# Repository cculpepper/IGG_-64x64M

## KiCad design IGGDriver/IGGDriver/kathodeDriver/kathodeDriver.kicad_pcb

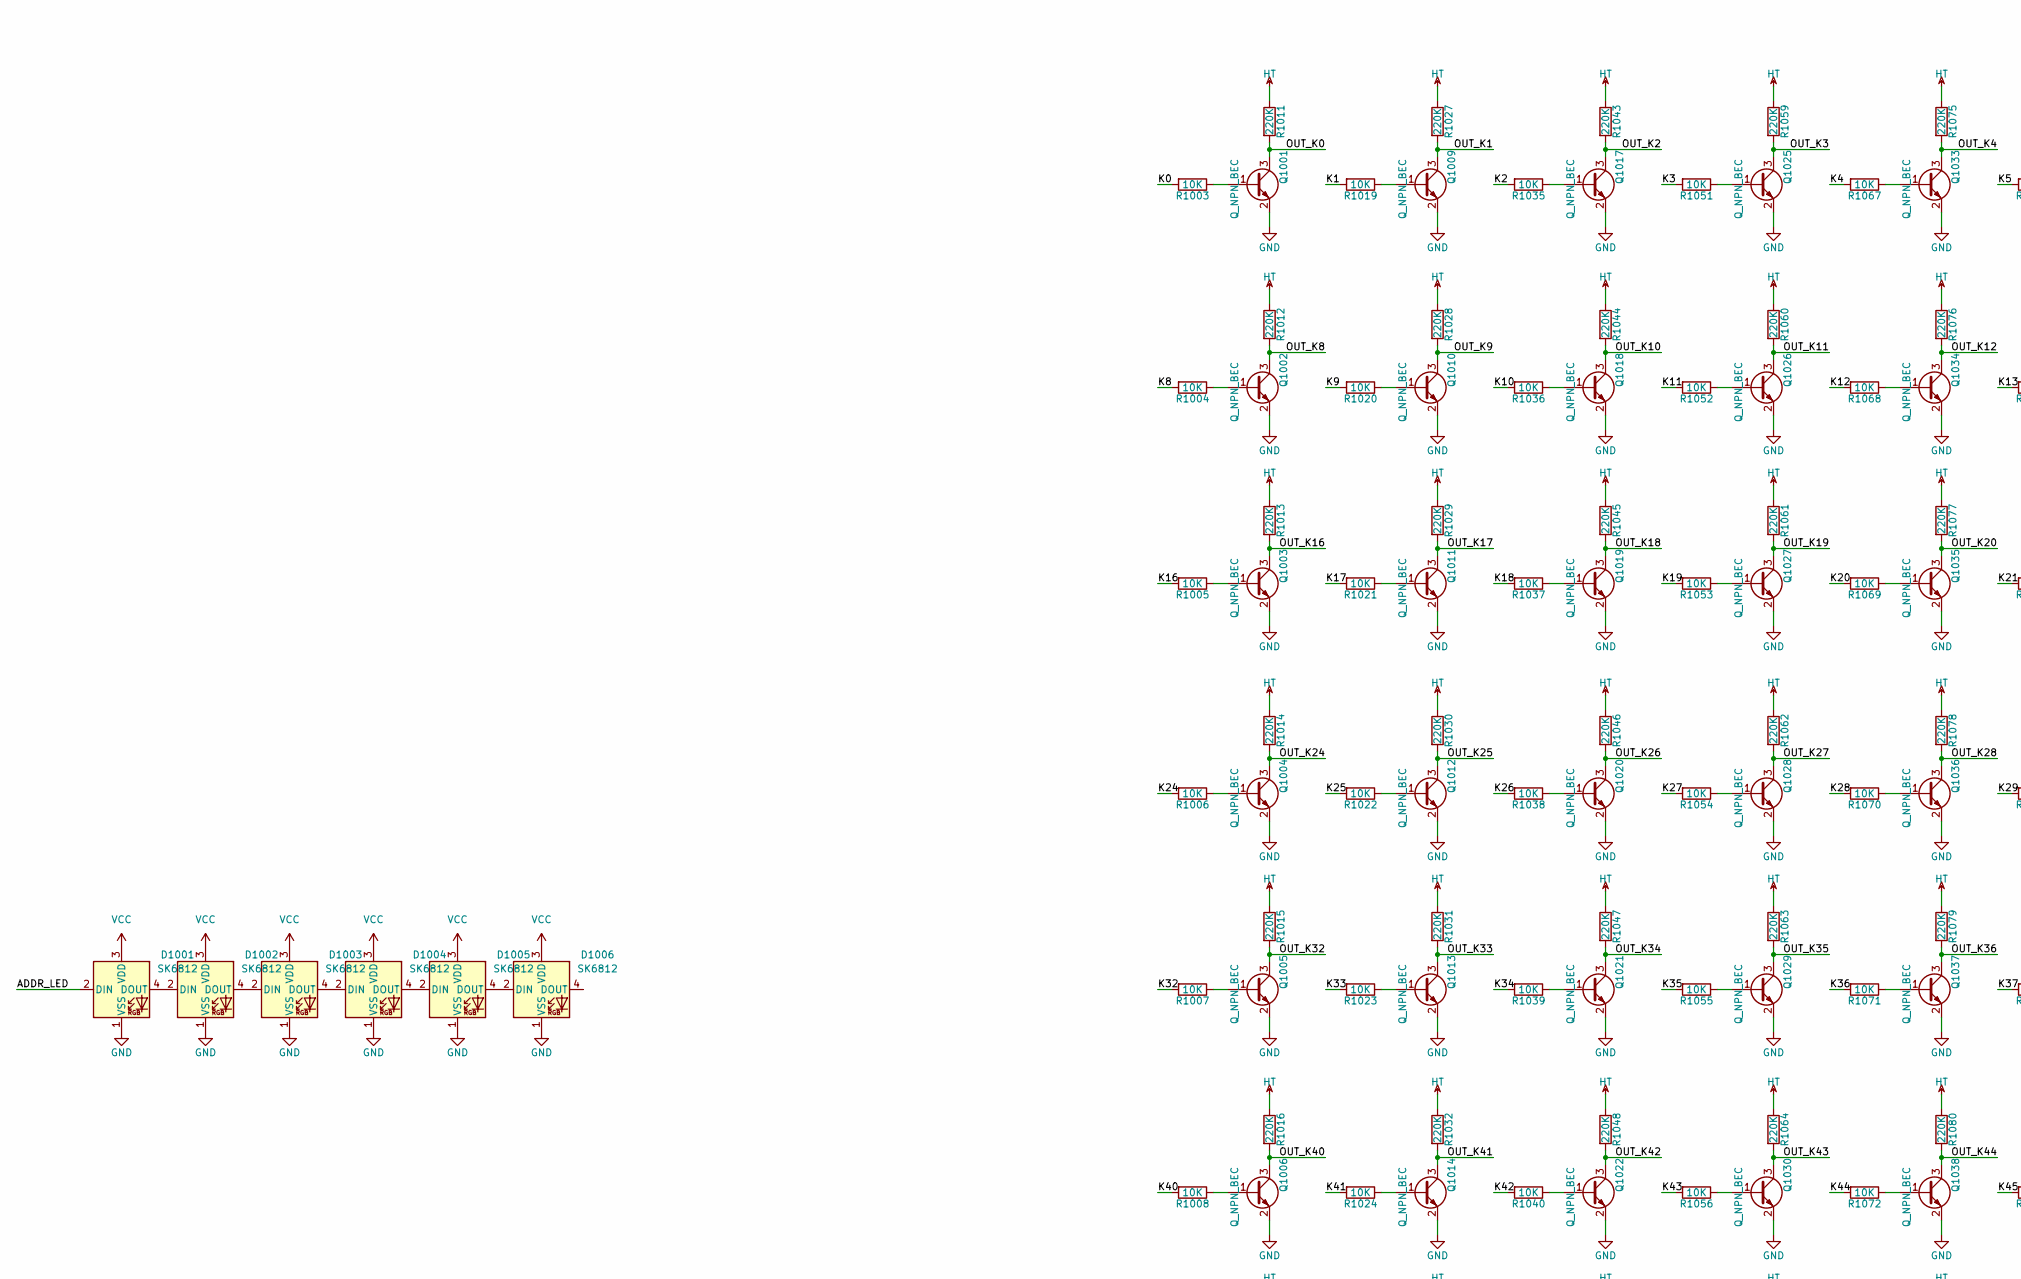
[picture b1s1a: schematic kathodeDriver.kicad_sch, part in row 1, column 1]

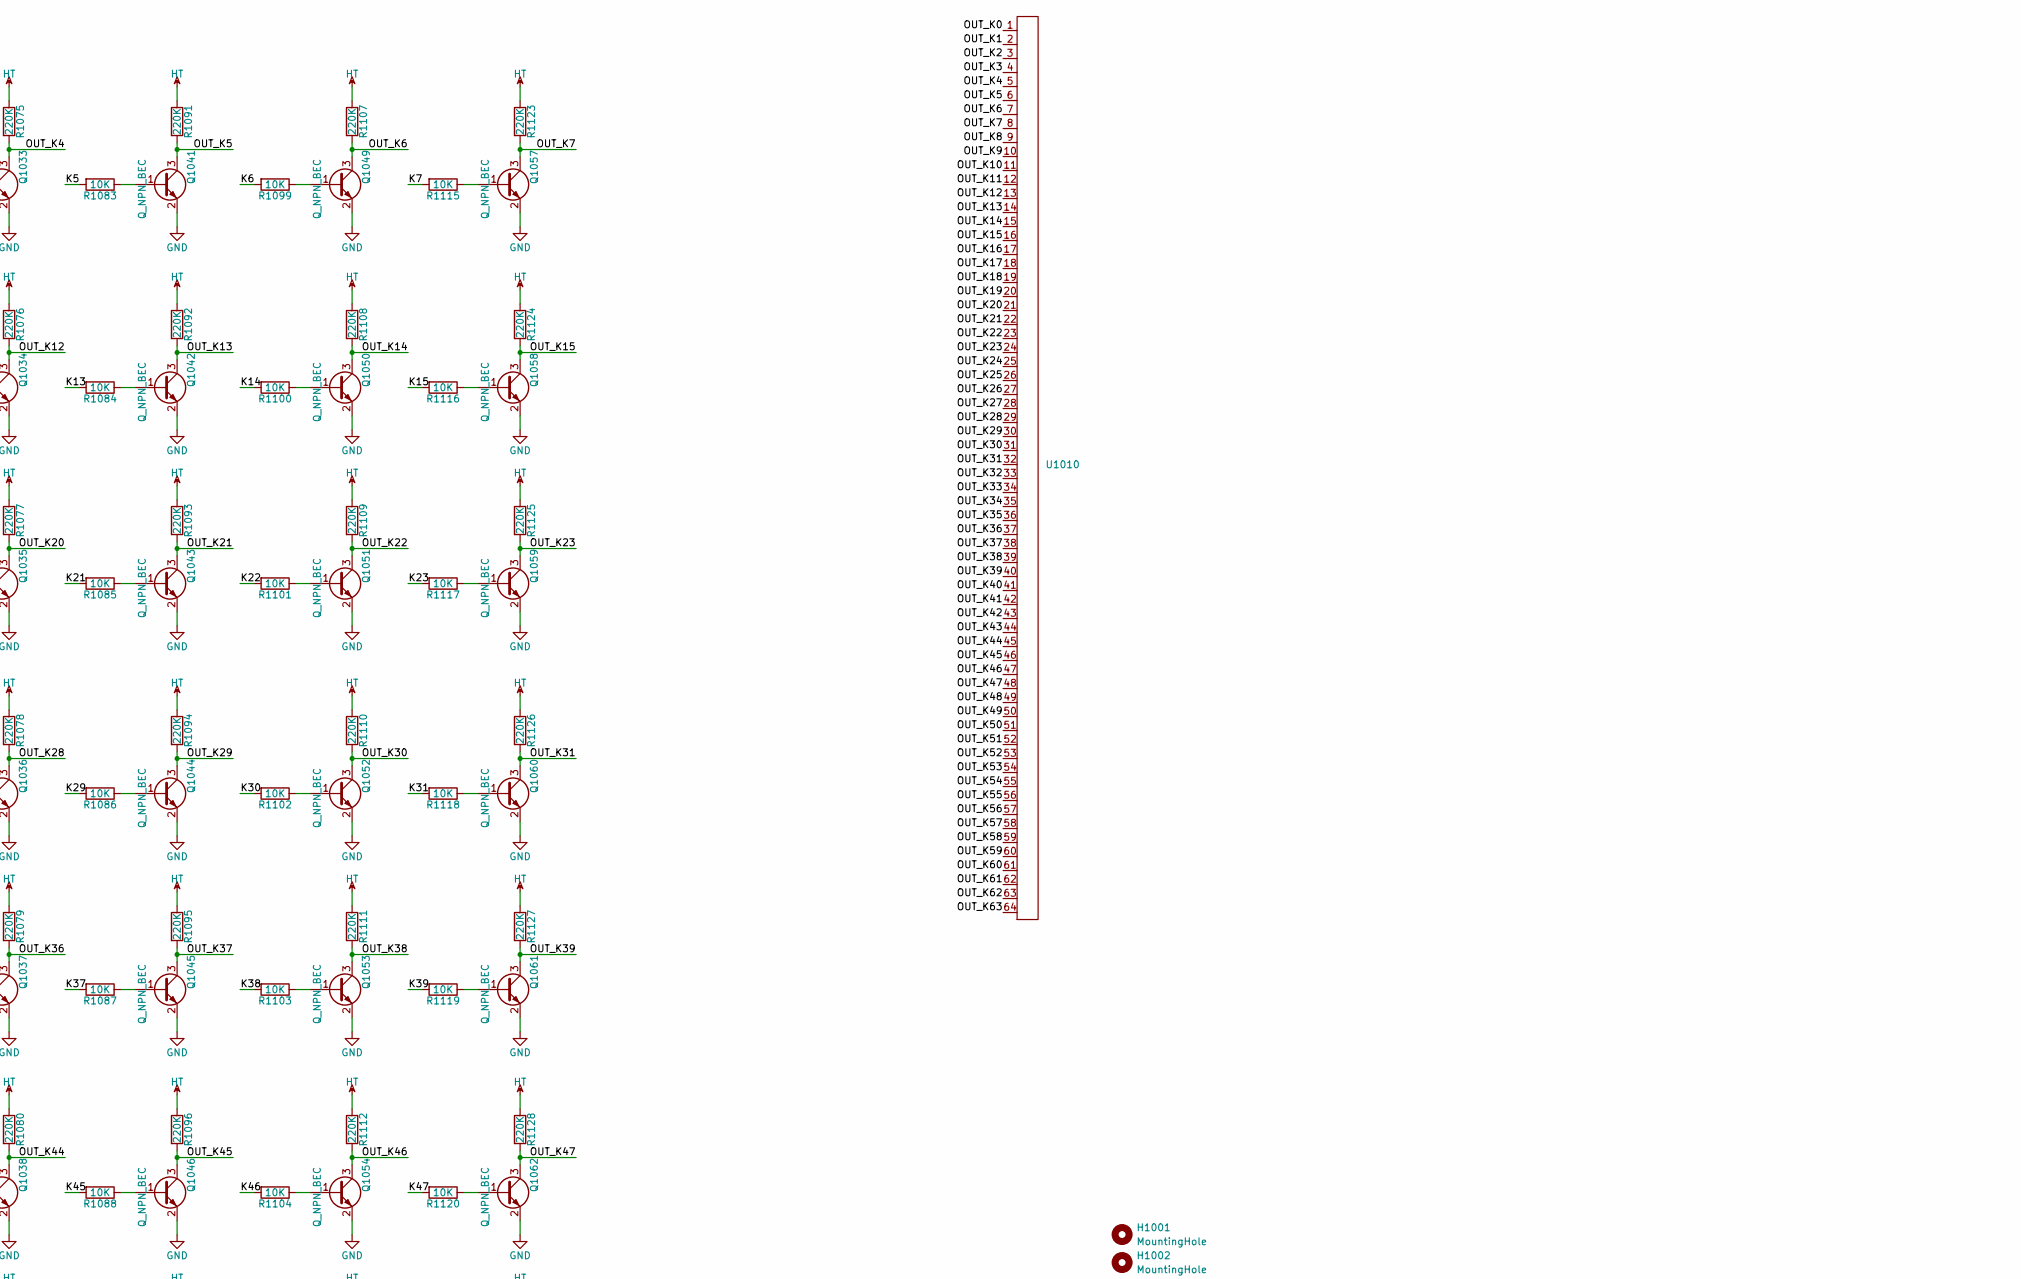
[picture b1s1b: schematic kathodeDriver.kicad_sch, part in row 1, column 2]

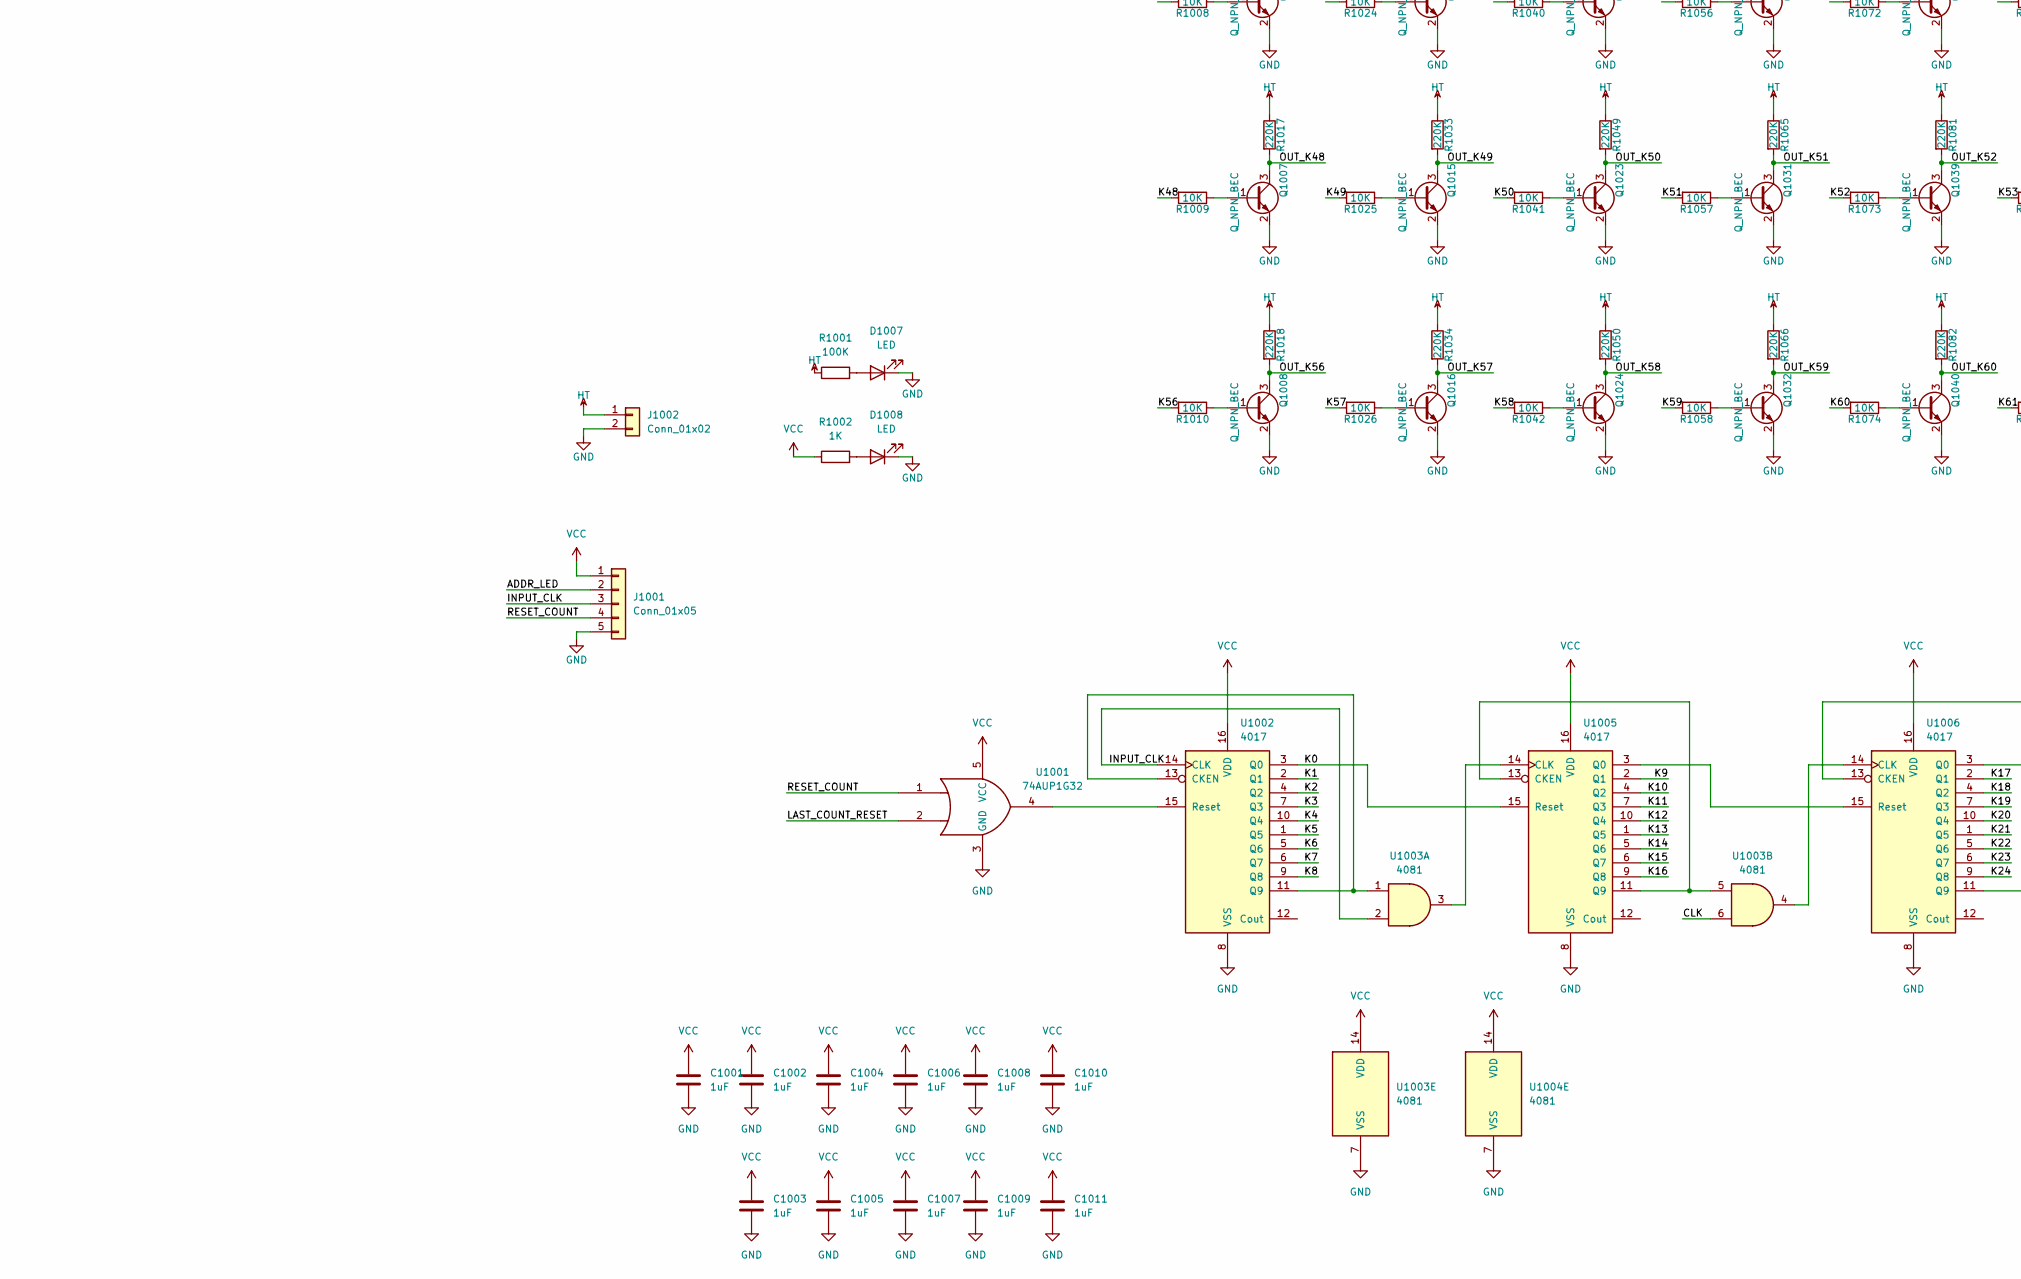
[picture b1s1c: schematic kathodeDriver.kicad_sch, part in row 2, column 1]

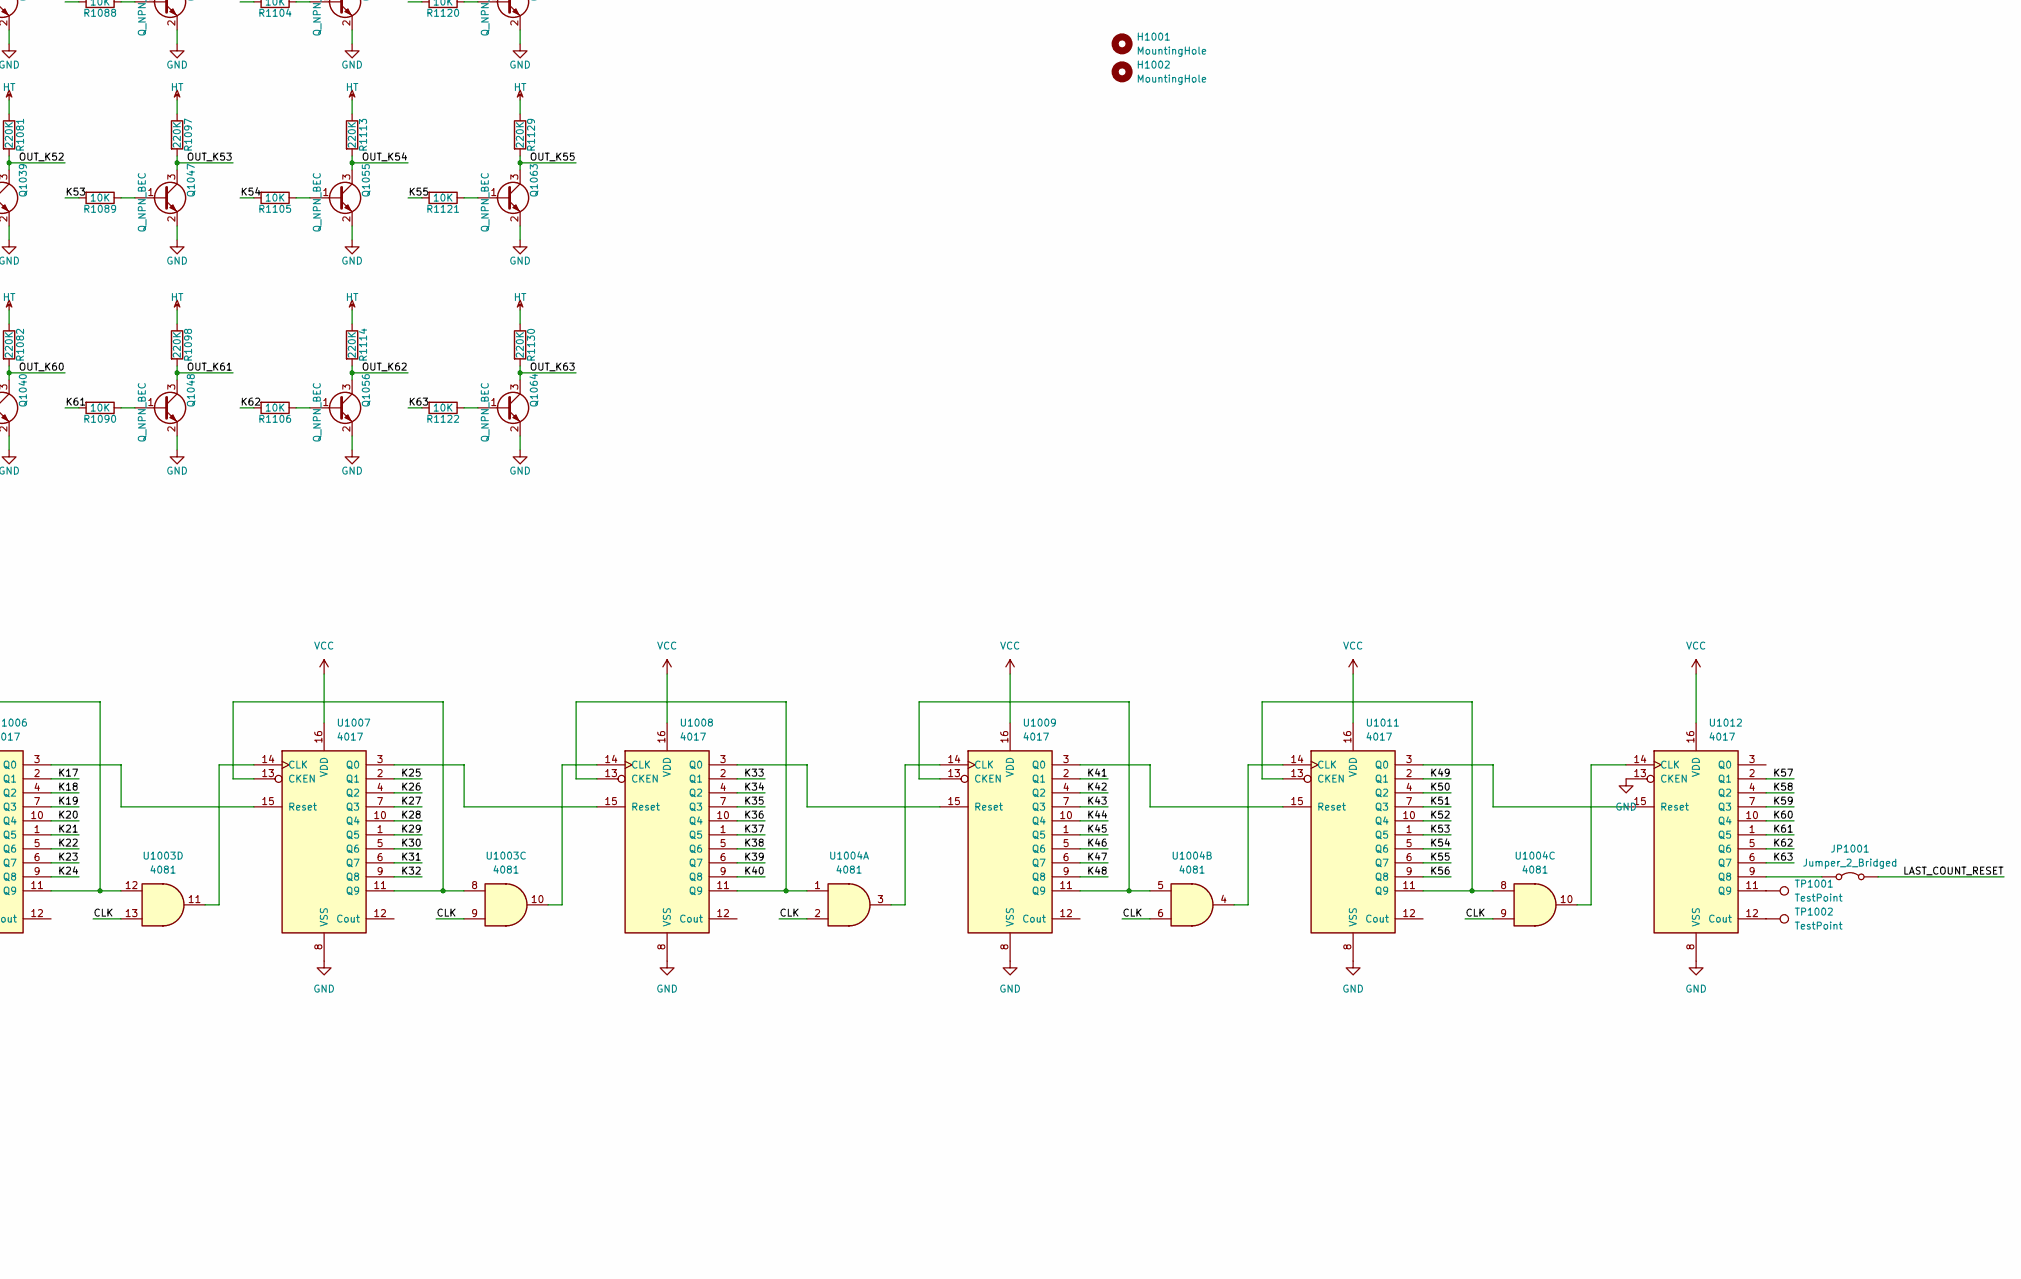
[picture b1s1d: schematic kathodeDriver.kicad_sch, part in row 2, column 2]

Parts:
C1001, C1002, C1003, C1004, C1005, C1006, C1007, C1008, C1009, C1010, C1011: 1uF; C_0603_1608Metric; LCSC C15849
D1001, D1002, D1003, D1004, D1005, D1006: SK6812; LED_SK6812_PLCC4_5.0x5.0mm_P3.2mm
D1007: LED; LED_0603_1608Metric; LCSC C72038
D1008: LED; LED_0603_1608Metric; LCSC C2286
H1001, H1002: MountingHole; Mounting_Wuerth_WA-SMSI-M3_H2mm_9774020360
J1001: Conn_01x05; JST_XH_B4B-XH-AM_1x05_P2.50mm_Vertical
J1002: Conn_01x02; JST_XH_B2B-XH-AM_1x02_P2.50mm_Vertical
JP1001: Jumper_2_Bridged; SolderJumper-2_P1.3mm_Bridged_RoundedPad1.0x1.5mm
Q1001, Q1002, Q1003, Q1004, Q1005, Q1006, Q1007, Q1008, Q1009, Q1010, Q1011, Q1012, Q1013, Q1014, Q1015, Q1016, Q1017, Q1018, Q1019, Q1020, Q1021, Q1022, Q1023, Q1024, Q1025, Q1026, Q1027, Q1028, Q1029, Q1030, Q1031, Q1032, Q1033, Q1034, Q1035, Q1036, Q1037, Q1038, Q1039, Q1040, Q1041, Q1042, Q1043, Q1044, Q1045, Q1046, Q1047, Q1048, Q1049, Q1050, Q1051, Q1052, Q1053, Q1054, Q1055, Q1056, Q1057, Q1058, Q1059, Q1060, Q1061, Q1062, Q1063, Q1064: Q_NPN_BEC; SOT-23; LCSC C20069141
R1001: 100K; R_0603_1608Metric; LCSC C25803
R1002: 1K; R_0603_1608Metric; LCSC C21190
R1003, R1004, R1005, R1006, R1007, R1008, R1009, R1010, R1019, R1020, R1021, R1022, R1023, R1024, R1025, R1026, R1035, R1036, R1037, R1038, R1039, R1040, R1041, R1042, R1051, R1052, R1053, R1054, R1055, R1056, R1057, R1058, R1067, R1068, R1069, R1070, R1071, R1072, R1073, R1074, R1083, R1084, R1085, R1086, R1087, R1088, R1089, R1090, R1099, R1100, R1101, R1102, R1103, R1104, R1105, R1106, R1115, R1116, R1117, R1118, R1119, R1120, R1121, R1122: 10K; R_0603_1608Metric; LCSC C25804
R1011, R1012, R1013, R1014, R1015, R1016, R1017, R1018, R1027, R1028, R1029, R1030, R1031, R1032, R1033, R1034, R1043, R1044, R1045, R1046, R1047, R1048, R1049, R1050, R1059, R1060, R1061, R1062, R1063, R1064, R1065, R1066, R1075, R1076, R1077, R1078, R1079, R1080, R1081, R1082, R1091, R1092, R1093, R1094, R1095, R1096, R1097, R1098, R1107, R1108, R1109, R1110, R1111, R1112, R1113, R1114, R1123, R1124, R1125, R1126, R1127, R1128, R1129, R1130: 220K; R_0805_2012Metric; LCSC C17556
TP1001, TP1002: TestPoint; TestPoint_Loop_D2.50mm_Drill1.0mm
U1001: 74AUP1G32; SOT-23-5; LCSC C7470
U1002, U1005, U1006, U1007, U1008, U1009, U1011, U1012: 4017; SOP-16_4.4x10.4mm_P1.27mm; LCSC C356694
U1003, U1004: 4081; SOIC-14_3.9x8.7mm_P1.27mm; LCSC C148318
U1010: IGG1

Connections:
/ADDR_LED: D1001.2 (DIN), J1001.2
/CLK: U1003.6, U1003.9, U1003.13, U1004.2, U1004.6, U1004.9
/INPUT_CLK: J1001.3, U1002.14 (CLK), U1003.2; also elsewhere on the board
/K0: R1003.2, U1002.3 (Q0), U1005.15 (Reset)
/K1: R1019.2, U1002.2 (Q1)
/K2: R1035.2, U1002.4 (Q2)
/K3: R1051.2, U1002.7 (Q3)
/K4: R1067.2, U1002.10 (Q4)
/K5: R1083.2, U1002.1 (Q5)
/K6: R1099.2, U1002.5 (Q6)
/K7: R1115.2, U1002.6 (Q7)
/K8: R1004.2, U1002.9 (Q8)
/K9: R1020.2, U1005.2 (Q1)
/K10: R1036.2, U1005.4 (Q2)
/K11: R1052.2, U1005.7 (Q3)
/K12: R1068.2, U1005.10 (Q4)
/K13: R1084.2, U1005.1 (Q5)
/K14: R1100.2, U1005.5 (Q6)
/K15: R1116.2, U1005.6 (Q7)
/K16: R1005.2, U1005.9 (Q8)
/K17: R1021.2, U1006.2 (Q1)
/K18: R1037.2, U1006.4 (Q2)
/K19: R1053.2, U1006.7 (Q3)
/K20: R1069.2, U1006.10 (Q4)
/K21: R1085.2, U1006.1 (Q5)
/K22: R1101.2, U1006.5 (Q6)
/K23: R1117.2, U1006.6 (Q7)
/K24: R1006.2, U1006.9 (Q8)
/K25: R1022.2, U1007.2 (Q1)
/K26: R1038.2, U1007.4 (Q2)
/K27: R1054.2, U1007.7 (Q3)
/K28: R1070.2, U1007.10 (Q4)
/K29: R1086.2, U1007.1 (Q5)
/K30: R1102.2, U1007.5 (Q6)
/K31: R1118.2, U1007.6 (Q7)
/K32: R1007.2, U1007.9 (Q8)
/K33: R1023.2, U1008.2 (Q1)
/K34: R1039.2, U1008.4 (Q2)
/K35: R1055.2, U1008.7 (Q3)
/K36: R1071.2, U1008.10 (Q4)
/K37: R1087.2, U1008.1 (Q5)
/K38: R1103.2, U1008.5 (Q6)
/K39: R1119.2, U1008.6 (Q7)
/K40: R1008.2, U1008.9 (Q8)
/K41: R1024.2, U1009.2 (Q1)
/K42: R1040.2, U1009.4 (Q2)
/K43: R1056.2, U1009.7 (Q3)
/K44: R1072.2, U1009.10 (Q4)
/K45: R1088.2, U1009.1 (Q5)
/K46: R1104.2, U1009.5 (Q6)
/K47: R1120.2, U1009.6 (Q7)
/K48: R1009.2, U1009.9 (Q8)
/K49: R1025.2, U1011.2 (Q1)
/K50: R1041.2, U1011.4 (Q2)
/K51: R1057.2, U1011.7 (Q3)
/K52: R1073.2, U1011.10 (Q4)
/K53: R1089.2, U1011.1 (Q5)
/K54: R1105.2, U1011.5 (Q6)
/K55: R1121.2, U1011.6 (Q7)
/K56: R1010.2, U1011.9 (Q8)
/K57: R1026.2, U1012.2 (Q1)
/K58: R1042.2, U1012.4 (Q2)
/K59: R1058.2, U1012.7 (Q3)
/K60: R1074.2, U1012.10 (Q4)
/K61: R1090.2, U1012.1 (Q5)
/K62: R1106.2, U1012.5 (Q6)
/K63: R1122.2, U1012.6 (Q7)
/LAST_COUNT_RESET: JP1001.2 (B), U1001.2
/OUT_K0: Q1001.3 (C), R1011.2, U1010.1
/OUT_K1: Q1009.3 (C), R1027.2, U1010.2
/OUT_K2: Q1017.3 (C), R1043.2, U1010.3
/OUT_K3: Q1025.3 (C), R1059.2, U1010.4
/OUT_K4: Q1033.3 (C), R1075.2, U1010.5
/OUT_K5: Q1041.3 (C), R1091.2, U1010.6
/OUT_K6: Q1049.3 (C), R1107.2, U1010.7
/OUT_K7: Q1057.3 (C), R1123.2, U1010.8
/OUT_K8: Q1002.3 (C), R1012.2, U1010.9
/OUT_K9: Q1010.3 (C), R1028.2, U1010.10
/OUT_K10: Q1018.3 (C), R1044.2, U1010.11
/OUT_K11: Q1026.3 (C), R1060.2, U1010.12
/OUT_K12: Q1034.3 (C), R1076.2, U1010.13
/OUT_K13: Q1042.3 (C), R1092.2, U1010.14
/OUT_K14: Q1050.3 (C), R1108.2, U1010.15
/OUT_K15: Q1058.3 (C), R1124.2, U1010.16
/OUT_K16: Q1003.3 (C), R1013.2, U1010.17
/OUT_K17: Q1011.3 (C), R1029.2, U1010.18
/OUT_K18: Q1019.3 (C), R1045.2, U1010.19
/OUT_K19: Q1027.3 (C), R1061.2, U1010.20
/OUT_K20: Q1035.3 (C), R1077.2, U1010.21
/OUT_K21: Q1043.3 (C), R1093.2, U1010.22
/OUT_K22: Q1051.3 (C), R1109.2, U1010.23
/OUT_K23: Q1059.3 (C), R1125.2, U1010.24
/OUT_K24: Q1004.3 (C), R1014.2, U1010.25
/OUT_K25: Q1012.3 (C), R1030.2, U1010.26
/OUT_K26: Q1020.3 (C), R1046.2, U1010.27
/OUT_K27: Q1028.3 (C), R1062.2, U1010.28
/OUT_K28: Q1036.3 (C), R1078.2, U1010.29
/OUT_K29: Q1044.3 (C), R1094.2, U1010.30
/OUT_K30: Q1052.3 (C), R1110.2, U1010.31
/OUT_K31: Q1060.3 (C), R1126.2, U1010.32
/OUT_K32: Q1005.3 (C), R1015.2, U1010.33
/OUT_K33: Q1013.3 (C), R1031.2, U1010.34
/OUT_K34: Q1021.3 (C), R1047.2, U1010.35
/OUT_K35: Q1029.3 (C), R1063.2, U1010.36
/OUT_K36: Q1037.3 (C), R1079.2, U1010.37
/OUT_K37: Q1045.3 (C), R1095.2, U1010.38
/OUT_K38: Q1053.3 (C), R1111.2, U1010.39
/OUT_K39: Q1061.3 (C), R1127.2, U1010.40
/OUT_K40: Q1006.3 (C), R1016.2, U1010.41
/OUT_K41: Q1014.3 (C), R1032.2, U1010.42
/OUT_K42: Q1022.3 (C), R1048.2, U1010.43
/OUT_K43: Q1030.3 (C), R1064.2, U1010.44
/OUT_K44: Q1038.3 (C), R1080.2, U1010.45
/OUT_K45: Q1046.3 (C), R1096.2, U1010.46
/OUT_K46: Q1054.3 (C), R1112.2, U1010.47
/OUT_K47: Q1062.3 (C), R1128.2, U1010.48
/OUT_K48: Q1007.3 (C), R1017.2, U1010.49
/OUT_K49: Q1015.3 (C), R1033.2, U1010.50
/OUT_K50: Q1023.3 (C), R1049.2, U1010.51
/OUT_K51: Q1031.3 (C), R1065.2, U1010.52
/OUT_K52: Q1039.3 (C), R1081.2, U1010.53
/OUT_K53: Q1047.3 (C), R1097.2, U1010.54
/OUT_K54: Q1055.3 (C), R1113.2, U1010.55
/OUT_K55: Q1063.3 (C), R1129.2, U1010.56
/OUT_K56: Q1008.3 (C), R1018.2, U1010.57
/OUT_K57: Q1016.3 (C), R1034.2, U1010.58
/OUT_K58: Q1024.3 (C), R1050.2, U1010.59
/OUT_K59: Q1032.3 (C), R1066.2, U1010.60
/OUT_K60: Q1040.3 (C), R1082.2, U1010.61
/OUT_K61: Q1048.3 (C), R1098.2, U1010.62
/OUT_K62: Q1056.3 (C), R1114.2, U1010.63
/OUT_K63: Q1064.3 (C), R1130.2, U1010.64
/RESET_COUNT: J1001.4, U1001.1; also elsewhere on the board
GND: C1001.2, C1002.2, C1003.2, C1004.2, C1005.2, C1006.2, C1007.2, C1008.2, C1009.2, C1010.2, C1011.2, D1001.1 (VSS), D1002.1 (VSS), D1003.1 (VSS), D1004.1 (VSS), D1005.1 (VSS), D1006.1 (VSS), D1007.1 (K), D1008.1 (K), J1001.5, J1002.2, Q1001.2 (E), Q1002.2 (E), Q1003.2 (E), Q1004.2 (E), Q1005.2 (E), Q1006.2 (E), Q1007.2 (E), Q1008.2 (E), Q1009.2 (E), Q1010.2 (E), Q1011.2 (E), Q1012.2 (E), Q1013.2 (E), Q1014.2 (E), Q1015.2 (E), Q1016.2 (E), Q1017.2 (E), Q1018.2 (E), Q1019.2 (E), Q1020.2 (E), Q1021.2 (E), Q1022.2 (E), Q1023.2 (E), Q1024.2 (E), Q1025.2 (E), Q1026.2 (E), Q1027.2 (E), Q1028.2 (E), Q1029.2 (E), Q1030.2 (E), Q1031.2 (E), Q1032.2 (E), Q1033.2 (E), Q1034.2 (E), Q1035.2 (E), Q1036.2 (E), Q1037.2 (E), Q1038.2 (E), Q1039.2 (E), Q1040.2 (E), Q1041.2 (E), Q1042.2 (E), Q1043.2 (E), Q1044.2 (E), Q1045.2 (E), Q1046.2 (E), Q1047.2 (E), Q1048.2 (E), Q1049.2 (E), Q1050.2 (E), Q1051.2 (E), Q1052.2 (E), Q1053.2 (E), Q1054.2 (E), Q1055.2 (E), Q1056.2 (E), Q1057.2 (E), Q1058.2 (E), Q1059.2 (E), Q1060.2 (E), Q1061.2 (E), Q1062.2 (E), Q1063.2 (E), Q1064.2 (E), U1001.3 (GND), U1002.8 (VSS), U1003.7 (VSS), U1004.7 (VSS), U1005.8 (VSS), U1006.8 (VSS), U1007.8 (VSS), U1008.8 (VSS), U1009.8 (VSS), U1011.8 (VSS), U1012.8 (VSS), U1012.13 (CKEN); also elsewhere on the board
HT: J1002.1, R1001.1, R1011.1, R1012.1, R1013.1, R1014.1, R1015.1, R1016.1, R1017.1, R1018.1, R1027.1, R1028.1, R1029.1, R1030.1, R1031.1, R1032.1, R1033.1, R1034.1, R1043.1, R1044.1, R1045.1, R1046.1, R1047.1, R1048.1, R1049.1, R1050.1, R1059.1, R1060.1, R1061.1, R1062.1, R1063.1, R1064.1, R1065.1, R1066.1, R1075.1, R1076.1, R1077.1, R1078.1, R1079.1, R1080.1, R1081.1, R1082.1, R1091.1, R1092.1, R1093.1, R1094.1, R1095.1, R1096.1, R1097.1, R1098.1, R1107.1, R1108.1, R1109.1, R1110.1, R1111.1, R1112.1, R1113.1, R1114.1, R1123.1, R1124.1, R1125.1, R1126.1, R1127.1, R1128.1, R1129.1, R1130.1
unnamed: D1001.4 (DOUT), D1002.2 (DIN)
unnamed: D1002.4 (DOUT), D1003.2 (DIN)
unnamed: D1003.4 (DOUT), D1004.2 (DIN)
unnamed: D1004.4 (DOUT), D1005.2 (DIN)
unnamed: D1005.4 (DOUT), D1006.2 (DIN)
unnamed: D1007.2 (A), R1001.2
unnamed: D1008.2 (A), R1002.2
unnamed: JP1001.1 (A), U1012.9 (Q8)
unnamed: Q1001.1 (B), R1003.1
unnamed: Q1002.1 (B), R1004.1
unnamed: Q1003.1 (B), R1005.1
unnamed: Q1004.1 (B), R1006.1
unnamed: Q1005.1 (B), R1007.1
unnamed: Q1006.1 (B), R1008.1
unnamed: Q1007.1 (B), R1009.1
unnamed: Q1008.1 (B), R1010.1
unnamed: Q1009.1 (B), R1019.1
unnamed: Q1010.1 (B), R1020.1
unnamed: Q1011.1 (B), R1021.1
unnamed: Q1012.1 (B), R1022.1
unnamed: Q1013.1 (B), R1023.1
unnamed: Q1014.1 (B), R1024.1
unnamed: Q1015.1 (B), R1025.1
unnamed: Q1016.1 (B), R1026.1
unnamed: Q1017.1 (B), R1035.1
unnamed: Q1018.1 (B), R1036.1
unnamed: Q1019.1 (B), R1037.1
unnamed: Q1020.1 (B), R1038.1
unnamed: Q1021.1 (B), R1039.1
unnamed: Q1022.1 (B), R1040.1
unnamed: Q1023.1 (B), R1041.1
unnamed: Q1024.1 (B), R1042.1
unnamed: Q1025.1 (B), R1051.1
unnamed: Q1026.1 (B), R1052.1
unnamed: Q1027.1 (B), R1053.1
unnamed: Q1028.1 (B), R1054.1
unnamed: Q1029.1 (B), R1055.1
unnamed: Q1030.1 (B), R1056.1
unnamed: Q1031.1 (B), R1057.1
unnamed: Q1032.1 (B), R1058.1
unnamed: Q1033.1 (B), R1067.1
unnamed: Q1034.1 (B), R1068.1
unnamed: Q1035.1 (B), R1069.1
unnamed: Q1036.1 (B), R1070.1
unnamed: Q1037.1 (B), R1071.1
unnamed: Q1038.1 (B), R1072.1
unnamed: Q1039.1 (B), R1073.1
unnamed: Q1040.1 (B), R1074.1
unnamed: Q1041.1 (B), R1083.1
unnamed: Q1042.1 (B), R1084.1
unnamed: Q1043.1 (B), R1085.1
unnamed: Q1044.1 (B), R1086.1
unnamed: Q1045.1 (B), R1087.1
unnamed: Q1046.1 (B), R1088.1
unnamed: Q1047.1 (B), R1089.1
unnamed: Q1048.1 (B), R1090.1
unnamed: Q1049.1 (B), R1099.1
unnamed: Q1050.1 (B), R1100.1
unnamed: Q1051.1 (B), R1101.1
unnamed: Q1052.1 (B), R1102.1
unnamed: Q1053.1 (B), R1103.1
unnamed: Q1054.1 (B), R1104.1
unnamed: Q1055.1 (B), R1105.1
unnamed: Q1056.1 (B), R1106.1
unnamed: Q1057.1 (B), R1115.1
unnamed: Q1058.1 (B), R1116.1
unnamed: Q1059.1 (B), R1117.1
unnamed: Q1060.1 (B), R1118.1
unnamed: Q1061.1 (B), R1119.1
unnamed: Q1062.1 (B), R1120.1
unnamed: Q1063.1 (B), R1121.1
unnamed: Q1064.1 (B), R1122.1
unnamed: U1002.11 (Q9), U1002.13 (CKEN), U1003.1
unnamed: U1001.4, U1002.15 (Reset)
unnamed: U1003.5, U1005.11 (Q9), U1005.13 (CKEN)
unnamed: U1003.3, U1005.14 (CLK)
unnamed: U1005.3 (Q0), U1006.15 (Reset)
unnamed: U1003.12, U1006.11 (Q9), U1006.13 (CKEN)
unnamed: U1003.4, U1006.14 (CLK)
unnamed: U1006.3 (Q0), U1007.15 (Reset)
unnamed: U1003.8, U1007.11 (Q9), U1007.13 (CKEN)
unnamed: U1003.11, U1007.14 (CLK)
unnamed: U1007.3 (Q0), U1008.15 (Reset)
unnamed: U1004.1, U1008.11 (Q9), U1008.13 (CKEN)
unnamed: U1003.10, U1008.14 (CLK)
unnamed: U1008.3 (Q0), U1009.15 (Reset)
unnamed: U1004.5, U1009.11 (Q9), U1009.13 (CKEN)
unnamed: U1004.3, U1009.14 (CLK)
unnamed: U1009.3 (Q0), U1011.15 (Reset)
unnamed: U1004.8, U1011.11 (Q9), U1011.13 (CKEN)
unnamed: U1004.4, U1011.14 (CLK)
unnamed: U1011.3 (Q0), U1012.15 (Reset)
unnamed: U1004.10, U1012.14 (CLK)
unnamed: TP1002.1, U1012.12 (Cout)
unnamed: TP1001.1, U1012.11 (Q9)
VCC: C1001.1, C1002.1, C1003.1, C1004.1, C1005.1, C1006.1, C1007.1, C1008.1, C1009.1, C1010.1, C1011.1, D1001.3 (VDD), D1002.3 (VDD), D1003.3 (VDD), D1004.3 (VDD), D1005.3 (VDD), D1006.3 (VDD), J1001.1, R1002.1, U1001.5 (VCC), U1002.16 (VDD), U1003.14 (VDD), U1004.14 (VDD), U1005.16 (VDD), U1006.16 (VDD), U1007.16 (VDD), U1008.16 (VDD), U1009.16 (VDD), U1011.16 (VDD), U1012.16 (VDD); also elsewhere on the board

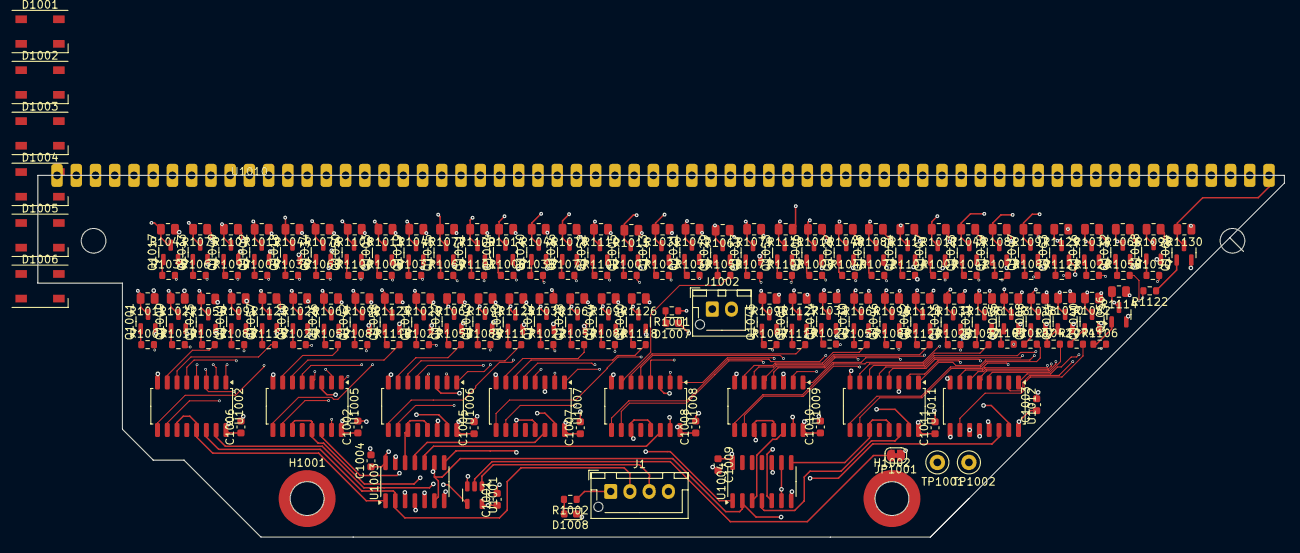
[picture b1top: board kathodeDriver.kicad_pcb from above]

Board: 4 copper layers, 162.0 x 47.0 mm, 232 parts (0 on the bottom side), 230 nets.

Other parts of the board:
J1: Conn_01x04; JST_XH_B4B-XH-AM_1x04_P2.50mm_Vertical

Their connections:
/INPUT_CLK: J1.2; also elsewhere on the board
/RESET_COUNT: J1.3; also elsewhere on the board
GND: J1.4; also elsewhere on the board
VCC: J1.1; also elsewhere on the board
